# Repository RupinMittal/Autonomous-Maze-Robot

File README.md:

# Autonomous Maze Robot

The top right corner is the end of the maze. See the Demo folder for full videos, and below for an overview
of the project. 

## Made with IEEE UCLA

### Description

This project is an autononmous maze navigating robot. It was built from scratch with 
the help of IEEE at UCLA (and my leads Bradley Schulz and Tyler Price).

To see the code, go to Code-SRC.
To run the code on your micromous, download the MicroMouse-STM32IDE.zip file, and open in the STM32 Cube IDE, 
so that you have the STM-configured files ready to go. Your robot will need to match the same port connections
in the schematics.

The test for the robots was a modified verison of the AAMC competition at UCLA where the top right corner is
considered the end of the maze.

### Software

The microcontroller used was the STM 32 Microcontoller, so the embedded programs were written in 
the C programming language. 

Includes:
- Motor Control (PID)
- IR Sensor based control
- Floodfill Algorithm
- Simulator (the base of the simulator was written by Tyler Price at IEEE)

The files included in this repository are only the code I wrote, and not the files automatically 
configured by the STM 32 Cube IDE. 

### Hardware 

The base PCB was built by Bradley Schulz and Tyler Price from IEEE UCLA. I have made 
my own schematic designs for the whole project (included in this repository). All schematics were 
made with EAGLE. I designed the IR sensor PCB from scratch using EAGLE software as well.

- Power Board Schematic
- H-Bridge Schematic
- IR Sensor PCB Board

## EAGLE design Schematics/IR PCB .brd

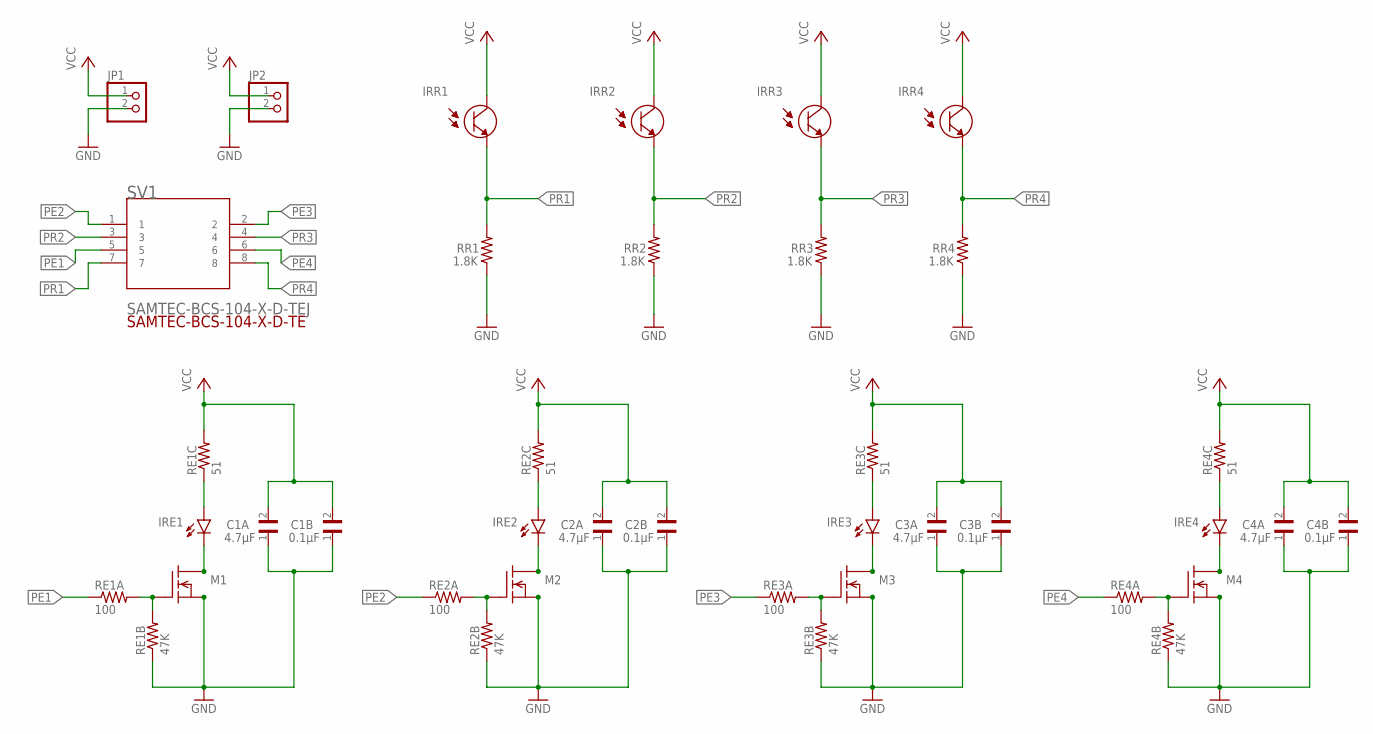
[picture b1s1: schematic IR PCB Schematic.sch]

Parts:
C1A, C2A, C3A, C4A: 4.7μF; CAPC2012X140N
C1B, C2B, C3B, C4B: 0.1μF; CAPC2012X140N
IRE1, IRE2, IRE3, IRE4: LED5MM
IRR1, IRR2, IRR3, IRR4: SFH_313_FA-3/4; XDCR_SFH_313_FA-3/4
JP1, JP2: PINHD-1X2; 1X02
M1, M2, M3, M4: 2N7002; SOT23
RE1A, RE2A, RE3A, RE4A: 100; R0805
RE1B, RE2B, RE3B, RE4B: 47K; R0805
RE1C, RE2C, RE3C, RE4C: 51; R0805
RR1, RR2, RR3, RR4: 1.8K; R0805
SV1: SAMTEC-BCS-104-X-D-TEJ; SAMTEC-BCS-104-X-D-TE

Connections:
GND: C1A.1, C1B.1, C2A.1, C2B.1, C3A.1, C3B.1, C4A.1, C4B.1, JP1.2, JP2.2, M1.2 (S), M2.2 (S), M3.2 (S), M4.2 (S), RE1B.1, RE2B.1, RE3B.1, RE4B.1, RR1.1, RR2.1, RR3.1, RR4.1
unnamed: M1.1 (G), RE1A.2, RE1B.2
unnamed: IRE1.A, RE1C.1
unnamed: M2.1 (G), RE2A.2, RE2B.2
unnamed: IRE2.A, RE2C.1
unnamed: IRE1.K (C), M1.3 (D)
unnamed: IRE2.K (C), M2.3 (D)
unnamed: M3.1 (G), RE3A.2, RE3B.2
unnamed: IRE3.A, RE3C.1
unnamed: IRE3.K (C), M3.3 (D)
unnamed: M4.1 (G), RE4A.2, RE4B.2
unnamed: IRE4.A, RE4C.1
unnamed: IRE4.K (C), M4.3 (D)
PE1: RE1A.1, SV1.5
PE2: RE2A.1, SV1.1
PE3: RE3A.1, SV1.2
PE4: RE4A.1, SV1.6
PR1: IRR1.1 (E), RR1.2, SV1.7
PR2: IRR2.1 (E), RR2.2, SV1.3
PR3: IRR3.1 (E), RR3.2, SV1.4
PR4: IRR4.1 (E), RR4.2, SV1.8
VCC: C1A.2, C1B.2, C2A.2, C2B.2, C3A.2, C3B.2, C4A.2, C4B.2, IRR1.2 (C), IRR2.2 (C), IRR3.2 (C), IRR4.2 (C), JP1.1, JP2.1, RE1C.2, RE2C.2, RE3C.2, RE4C.2

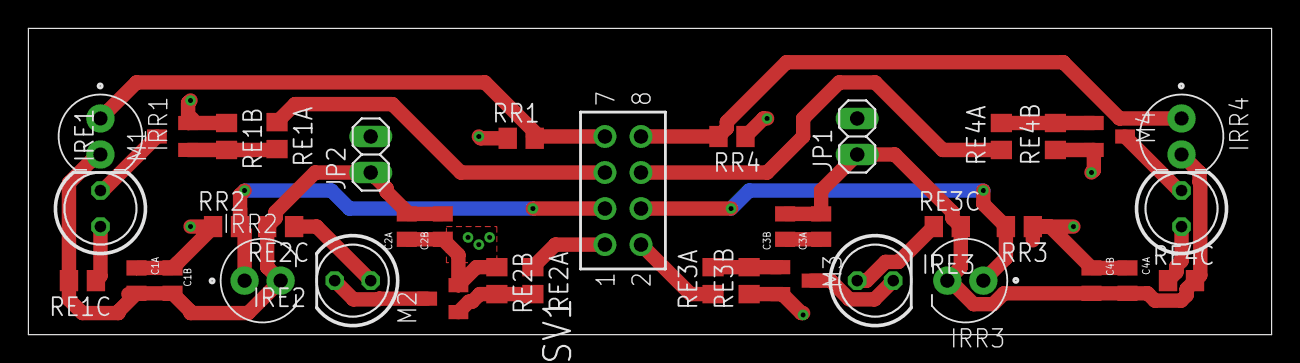
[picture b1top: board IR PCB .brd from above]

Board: 2 copper layers, 87.6 x 21.6 mm, 39 parts (0 on the bottom side), 22 nets.

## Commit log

2020-11-12 Initial Commit - README
2020-11-12 LED Switch code (works)
2020-11-12 Encoder code to get encoder counts (works)
2020-11-12 Basic motor movement code
2020-11-12 Power Regulator and H-Bridge Schematics
2020-11-26 PD Controller Design Doc
2020-12-22 PID control for straight line
2020-12-24 Removed some uneeded lines
2021-01-04 Code to make 90 degree turns
2021-01-13 Fixed bugs in code to turn, added code to move forward/back (works)
2021-01-30 Draft of IR PCB
2021-08-26 Added simulator (Tyler Price provided the underlying code)
2021-08-27 Reformatted all the code, added STM-configured zip file
2021-08-27 Additional Schematics/PCBs
2021-08-27 Renamed Files:
2021-08-27 Added demo videos
2021-08-27 Compressed size of demo videos
2021-08-27 Add video 1 to README
2021-08-27 Afixing video 1 bug
2021-08-27 Using gifs instead of videos
2021-08-27 Add both GIFs
2021-08-27 Added Image of robot
2021-08-27 Fix bug in Robot image
